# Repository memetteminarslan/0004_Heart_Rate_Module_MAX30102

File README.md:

# 0004_Heart_Rate_Module_MAX30102
You are seeing a large number of widely used Heart Rate modules in electronic development kits. More information coming soon...

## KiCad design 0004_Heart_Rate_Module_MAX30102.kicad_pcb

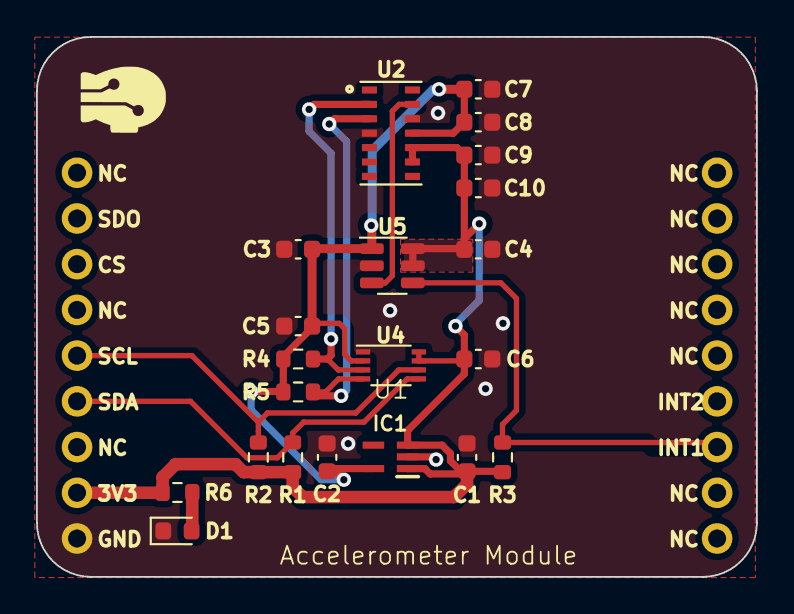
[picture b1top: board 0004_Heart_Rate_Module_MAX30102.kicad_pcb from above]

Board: 2 copper layers, 40.0 x 30.0 mm, 22 parts (0 on the bottom side), 10 nets.

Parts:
C1, C2: 10uF; C_0603_1608Metric
C3, C4, C5, C6, C7, C9, C10: 0,10uF; C_0603_1608Metric
C8: 4,7uF; C_0603_1608Metric
D1: LED; LED_0603_1608Metric
IC1: MAX8511EXK18+T; SOT65P210X110-5N
R1, R2, R3: 4.7k; R_0603_1608Metric
R4, R5: 1k; R_0603_1608Metric
R6: 470r; R_0603_1608Metric
U1: air_module
U2: MAX30102EFD+; MAX30102
U4: PCA9306; VSSOP-8_2.3x2mm_P0.5mm
U5: SN74LVC1T45DBV; SOT-23-6

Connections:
+1V8: C2.1, C3.1, C5.1, C7.1, C8.1, IC1.5 (OUT), R4.1, R5.1, U2.11 (VDD), U4.2 (VREF1), U5.1 (VCCA)
+3V3: C1.1, C4.1, C6.1, C9.1, C10.1, IC1.1 (IN), IC1.3 (~SHDN), R1.1, R2.1, R3.1, R6.1, U1.8 (3V3), U2.9 (VLED+), U2.10 (VLED+), U4.7 (VREF2), U4.8 (EN), U5.5 (DIR), U5.6 (VCCB)
GND: C1.2, C2.2, C3.2, C4.2, C5.2, C6.2, C7.2, C8.2, C9.2, C10.2, D1.1 (K), IC1.2 (GND), U1.9 (GND), U2.4 (PGND), U2.12 (GND), U4.1 (GND), U5.2 (GND)
INT: R3.2, U1.12 (GPIO), U5.4 (B)
INT_: U2.13 (~INT), U5.3 (A)
unnamed: D1.2 (A), R6.2
SCL: R2.2, U1.5 (SCL), U4.6 (SCL2)
SCL_: R4.2, U2.2 (SCL), U4.3 (SCL1)
SDA: R1.2, U1.6 (SDA), U4.5 (SDA2)
SDA_: R5.2, U2.3 (SDA), U4.4 (SDA1)
